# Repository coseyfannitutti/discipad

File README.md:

# discipad
 17-key numpad assembled with only through hole components, including usb type-c

[BOM, Build Guide, and Flashing Information](./doc)

Kits available at [cftkb.com](https://www.cftkb.com)

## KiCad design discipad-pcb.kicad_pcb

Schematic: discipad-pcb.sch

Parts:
BOOT1: BOOT
C1, C2: 22p; C_Disc_D3.0mm_W1.6mm_P2.50mm
C3: 4.7u; CP_Radial_D4.0mm_P1.50mm
C4, C5: 0.1u; C_Disc_D4.3mm_W1.9mm_P5.00mm
D1, D2, D3, D4, D5, D6, D7, D8, D9, D10, D11, D12, D13, D14, D15, D16, D17: D_DO-35_SOD27_P5.08mm_Horizontal
D18, D19: 3.6V; D_DO-35_SOD27_P5.08mm_Horizontal
F1: 500mA; polyfuse_5.1mm
J1: AVR-ISP-6
LED1: POWER
R1: 1.5K; R_Axial_DIN0204_L3.6mm_D1.6mm_P5.08mm_Horizontal
R2, R3: 5.1K; R_Axial_DIN0204_L3.6mm_D1.6mm_P5.08mm_Horizontal
R4, R5: 75R; R_Axial_DIN0204_L3.6mm_D1.6mm_P5.08mm_Horizontal
R6: 10K; R_Axial_DIN0204_L3.6mm_D1.6mm_P5.08mm_Horizontal
R7: 1.5K
RESET1: RESET; SW_PUSH_6mm
SW0, SW1, SW2, SW3, SW4, SW5, SW6, SW8, SW9, SW10, SW11, SW12, SW13, SW16: KEYSW; SW_Cherry_MX1A_1.00u_PCB-NOSCREEN
SW7, SW14: KEYSW; SW_Cherry_MX1A_2.00u_Vertical_PCB
SW15: KEYSW; SW_Cherry_MX1A_2.00u_PCB_FLIPPED
U1: ATmega328P-PU; DIP-28_W7.62mm
USB1: USB_C_GCT_USB4085
Y1: Crystal; Crystal_HC49-4H_Vertical

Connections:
D+: R5.1, U1.4 (PD2)
D-: R4.2, U1.5 (PD3)
GND: BOOT1.1, C1.2, C2.2, C3.2, C4.2, C5.2, D18.2, D19.2, J1.6 (GND), R2.1, R3.1, RESET1.1, U1.8 (GND), U1.22 (GND), USB1.A1, USB1.A12, USB1.B1, USB1.B12, USB1.S1
unnamed: D1.2, SW0.2
unnamed: D2.2, SW1.2
unnamed: D3.2, SW2.2
unnamed: D4.2, SW3.2
unnamed: D5.2, SW4.2
unnamed: D6.2, SW5.2
unnamed: D7.2, SW6.2
unnamed: D8.2, SW8.2
unnamed: D9.2, SW9.2
unnamed: D10.2, SW10.2
unnamed: D11.2, SW7.2
unnamed: D12.2, SW11.2
unnamed: D13.2, SW12.2
unnamed: D14.2, SW13.2
unnamed: D15.2, SW15.2
unnamed: D16.2, SW16.2
unnamed: D17.2, SW14.2
unnamed: D18.1, R1.2, R4.1, USB1.A7, USB1.B7
unnamed: D19.1, R5.2, USB1.A6, USB1.B6
unnamed: R2.2, USB1.A5
unnamed: R3.2, USB1.B5
VCC: F1.2, USB1.A4, USB1.A9, USB1.B4, USB1.B9
boot: BOOT1.2, U1.11 (PD5)
col0: SW0.1, SW4.1, SW8.1, SW11.1, SW15.1, U1.23 (PC0)
col1: SW1.1, SW5.1, SW9.1, SW12.1, U1.24 (PC1)
col2: SW2.1, SW6.1, SW10.1, SW13.1, SW16.1, U1.25 (PC2)
col3: SW3.1, SW7.1, SW14.1, U1.26 (PC3)
miso: J1.1 (MISO), U1.18 (PB4)
mosi: J1.4 (MOSI), U1.17 (PB3)
reset: J1.5 (~RST), R6.2, RESET1.2, U1.1 (~RESET~/PC6)
row0: D1.1, D2.1, D3.1, D4.1, U1.15 (PB1)
row1: D5.1, D6.1, D7.1, U1.14 (PB0)
row2: D8.1, D9.1, D10.1, D11.1, U1.13 (PD7)
row3: D12.1, D13.1, D14.1, U1.12 (PD6)
row4: D15.1, D16.1, D17.1, U1.6 (PD4)
sck: J1.3 (SCK), U1.19 (PB5)
xtal1: C1.1, U1.9 (XTAL1/PB6), Y1.1
xtal2: C2.1, U1.10 (XTAL2/PB7), Y1.2

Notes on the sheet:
MCU
USB/FUSE
POWER LED
ISP

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
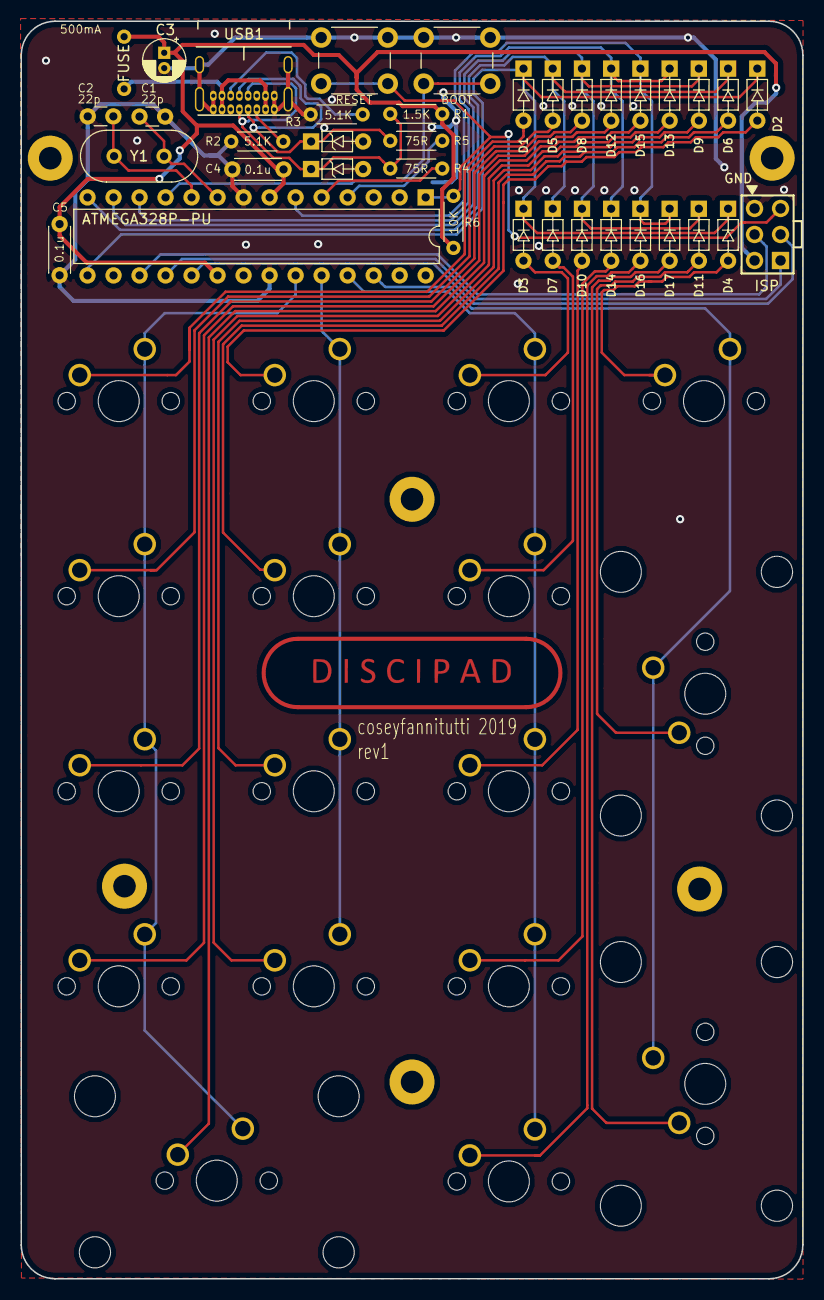
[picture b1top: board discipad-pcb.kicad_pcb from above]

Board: 2 copper layers, 76.3 x 122.8 mm, 54 parts (0 on the bottom side), 42 nets.

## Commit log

2019-09-21 Update fp-info-cache
2020-03-07 Create sym-lib-table
2020-03-07 Create discipad-pcb.sch-bak
